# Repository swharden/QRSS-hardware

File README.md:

# QRSS Hardware

This repository is an evolving collection of notes and resources related to QRSS hardware (TX and RX) that I (Scott Harden, AJ4VD) find useful. Eventually this work will become a webpage, but for now it's a GitHub repository which makes it easy to edit.

* **[Recently spotted AJ4VD QRSS signals](/spots)**
* Hardware notes are in the [builds](/builds) folder 
* New to QRSS?
  * [What is QRSS?](https://www.qsl.net/m0ayf/What-is-QRSS.html)
  * Join the [_QRSS Knights_ mailing list](https://groups.io/g/qrssknights)
  * See live signals around the world with [QRSS Plus](http://www.swharden.com/qrss/plus/)

### Modular QRSS Transmitter for Experimentation

The transmitter I built uses separate modules. I designed my transmitter this way so I can get a signal on the air, then work toward improving individual modules individually. My current design supports FSK (frequency-shift keying), OOK (on-off keying), and adjustable power output, and synchronization with GPS time. 

Modules are all individually powered and use SMA connectors for inputs/outputs. By applying this [SOLID](https://www.youtube.com/watch?v=TMuno5RZNeE&t=15m50s) principle to hardware development, the system easy to refactor (because it reduces _coupling_) and individual units are easy to test (because they have a defined _interface_).

* **oscillator** - Colpitts, 10.140 MHz crystal, no inductors (so SMT PCB is easy), outputs about 1 mW
* **oscillator oven** - uses two power 50 Ohm resistors to heat the _entire oscillator enclosure_ to above ambient room temperature. Thermistor is used for temperature sensation. By heating an entire metal-enclosed oscillator module, the entire oscillator circuitry (not just the crystal) becomes thermo-stable.
* **keyer** - based on an ATTiny2313 microcontroller. Keying is pulse-width modulated (PWM), and OOK output is also provided. Keyer has voltage combiner which has separate knobs to adjust center frequency and FSK width. Output is a single voltage for the oscillator, and a signal voltage for the amplifier. While it's currently configured for OOK, an analog voltage could be sent to the amplifier to control power output from software.
* **GPS** - To start messages at precise 10 minute intervals a GPS module (Neo-6M) is used. Rather than tap into the 1PPS signal line, I'm using the microcontroller to parse the serial data coming off the chip and begin transmitting at precise times.
* **amplifier** - currently an IRF510 final transistor with  74HC541 buffer pre-amplifier. The 74HC541's enable lines are controlled by the keyer to provide OOK. A potentiometer sets the power output. The current design has been tested to over 10W but this is an unnecessary (and undesirable) power level for QRSS.
* **frequency counter** - this is an independent project at the moment. I'm creating a USB frequency counter which will be useful for graphing frequency stability over time (and its relationship with temperature). I'll link to this once I have it tested/working.
* **antenna** - 30m dipole in my attic (Gainesville, Florida, USA)

### Photographs

This is a work in progress so the enclosures (if they even exist) are pretty crude. Additional photographs (and schematics) at various stages of the design process can be found in sub-folders of this repository. As individual modules are improved, these photographs will be updated.

### Project goals

I experimented with QRSS on and off over the last decade, but all of my designs were pretty crude. Now that I have more experience, knowledge, and resources, I'd like to get back into the hobby.

There are a lot of crystal oven designs and chassis heater designs out there, and I'd like to get better at testing different designs. This requires precision temperature and frequency measurements and involves using a PC for data-logging and analysis. I'd like to get a better understanding of the temperature vs. frequency profile not just of crystals, but of the entire oscillator circuit. I'm interested in developing a SMT oscillator board with the temperature controller built-in (using SMT resistors to heat the PCB, temperature-stabilizing the entire oscillator rather than just the crystal).

I'd also like to improve QRSS Plus, and see about creating an open-source QRSS spectrograph like Argo now that I have experience developing Windows applications with C#. While my previous efforts (in Python) were interesting, I now have a strong appreciation for click-to-run software that works with minimal complexity.

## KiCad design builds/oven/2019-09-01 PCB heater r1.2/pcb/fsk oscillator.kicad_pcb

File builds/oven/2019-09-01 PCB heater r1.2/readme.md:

# PCB Heater r1.2

The ultimate goal is to create a thermo-stable oscillator by heating the PCB to above ambient temperature (about 120F). This board tests how effective 8x 330 Ohm resistors can be at heating a 5cm x 5cm PCB. 

* A 10K NTC thermistor senses temperature in the center of the board
* At 12V each 330 Ohm resistor passes 36.3 mA (437 mW)
* Total max heating power is around 3.5 W
* The transistor also serves as a heating element

## Build Notes

_I ordered this board on 2019-09-01_

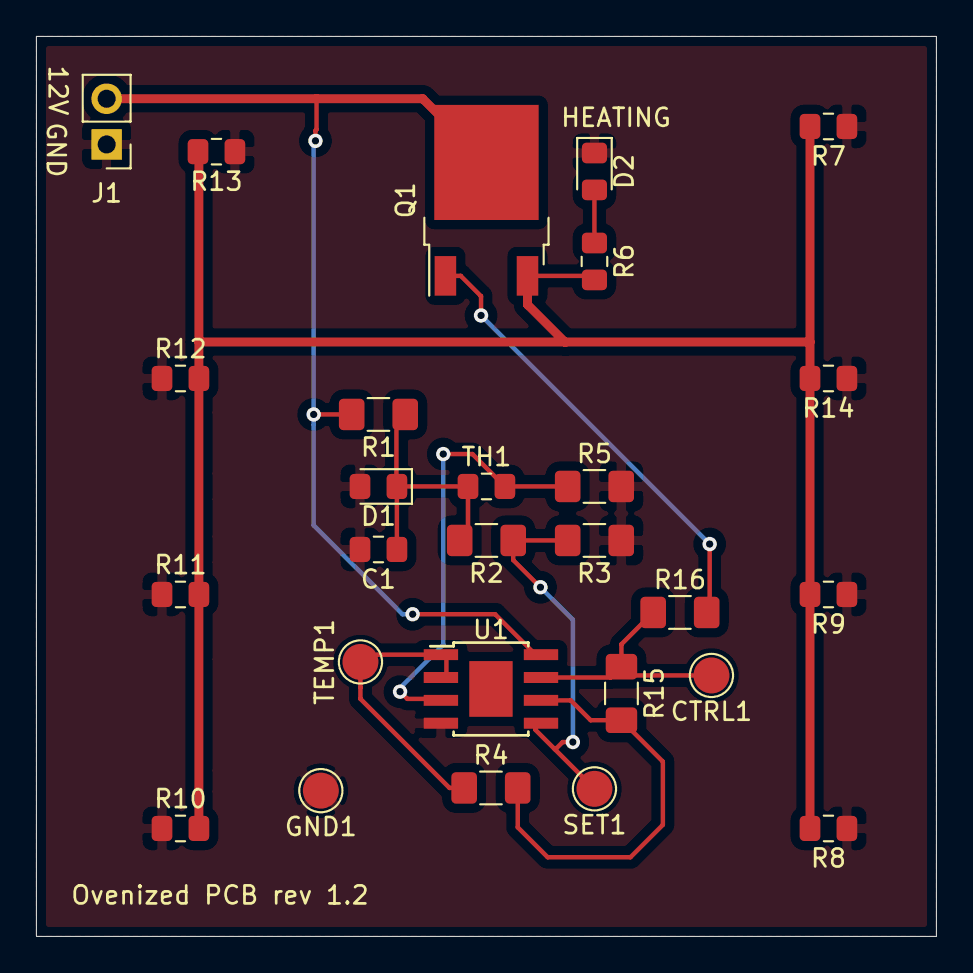
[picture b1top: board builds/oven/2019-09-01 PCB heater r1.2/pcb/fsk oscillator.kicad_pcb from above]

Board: 2 copper layers, 50.0 x 50.0 mm, 27 parts (0 on the bottom side), 11 nets.

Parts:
C1: .1u; C_0805_2012Metric_Pad1.15x1.40mm_HandSolder
CTRL1: TestPoint; TestPoint_Pad_D2.0mm
D1: 10V; D_0805_2012Metric_Pad1.15x1.40mm_HandSolder
D2: HEATING; LED_0805_2012Metric_Pad1.15x1.40mm_HandSolder
GND1: TestPoint; TestPoint_Pad_D2.0mm
J1: Conn_01x02_Male; PinHeader_1x02_P2.54mm_Vertical
Q1: MJD122; TO-252-2
R1, R4, R16: 1k; R_1206_3216Metric_Pad1.42x1.75mm_HandSolder
R2, R3, R5, R15: 10k; R_1206_3216Metric_Pad1.42x1.75mm_HandSolder
R6: 10k; R_0805_2012Metric_Pad1.15x1.40mm_HandSolder
R7, R8, R9, R10, R11, R12, R13, R14: 330; R_0805_2012Metric_Pad1.15x1.40mm_HandSolder
SET1: TestPoint; TestPoint_Pad_D2.0mm
TEMP1: TestPoint; TestPoint_Pad_D2.0mm
TH1: NTC; R_0805_2012Metric_Pad1.15x1.40mm_HandSolder
U1: LM358_DFN; TI_SO-PowerPAD-8

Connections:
+12V: J1.2, Q1.2, R1.2, U1.8
GND: C1.2, D1.2, D2.1, GND1.1, J1.1, R3.1, R5.2, R7.1, R8.1, R9.1, R10.1, R11.1, R12.1, R13.1, R14.1, U1.4
unnamed: CTRL1.1, R15.1, R16.1, U1.7
unnamed: D2.2, R6.1
unnamed: Q1.1, R16.2
unnamed: Q1.3, R6.2, R7.2, R8.2, R9.2, R10.2, R11.2, R12.2, R13.2, R14.2
unnamed: R2.1, R3.2, SET1.1, U1.5
unnamed: R4.1, TEMP1.1, U1.1, U1.2
unnamed: R5.1, TH1.2, U1.3
unnamed: R4.2, R15.2, U1.6
REF: C1.1, D1.1, R1.1, R2.2, TH1.1

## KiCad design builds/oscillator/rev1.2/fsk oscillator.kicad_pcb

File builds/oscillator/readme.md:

# QRSS Oscillator

This page documents development of a voltage-controlled oscillator suitable for QRSS. The oscillator project is developed in concert with the oven project.

## Varactor FSK Designs for QRSS

For QRSS it's convenient to have 2 frequency shift adjustments: a coarse one to set frequency (~200 Hz), and a fine one for FSK (5 Hz). 

Most QRSS TX designs use a variable capacitor to set the coarse adjustment, but I don't like that design because it means you have to open your enclosure every time you want to shift frequency:

VK2ZAY shows a design that pulls one leg of a crystal using two varactors, the magnitude of each is controlled by a series capacitor:

I tried building designs like this I find them very frustrating. 

Issue 1: coarse adjustment modifies FSK shift.
Every time I adjust the coarse voltage, the FSK distance changes. Consider a coarse adjustment resulting in a small capacitance: the fine FSK can produce a large shift. When the coarse produces a large capacitance, the fine FSK has little effect. If your fine FSK is a perfect 5Hz and you adjust the coarse frequency, your FSK is no longer 5Hz.

Issue 2: ~varactor diodes are too variable at low voltages. For stable operation it helps to run a varactor at several volts. I fix this by running the FSK voltage through a voltage divider _to VCC_ (not ground), and use the high-pulled fractional voltage on the varactor.~ Actually this was only a problem for reverse-biased LEDs. Real varactor diodes worked fine at low voltages.

***NOTE TO SELF: Use a real varicap diode! You have [BB132](https://uk.rs-online.com/webdocs/0466/0900766b80466490.pdf) (around 60 pF) and [BB149A](http://pdf.datasheetcatalog.com/datasheet/NXP_Semiconductors/BB149A.pdf) (around 20 pF) so you can get tons of swing by using one! Stop using reverse-biased LEDs!*** A reverse-biasd blue LED measured 60 Hz swing (with a lot of additional fixed capacitance in place to get near center frequency). Replacing this with a BB132 (I had to remove a 5pA cap to compensate) I got a swing of 159 Hz. That's more than double, and that's just one varicap. You can stack them in parallel. **Real varicaps dont mind low voltage*** I found out, so don't worry about avoiding that super low region like with the LED.

This is a design I came up with that seems to be treating me well so far. Fixed capacitors (optionally populated) set the frequency so the crystal oscillates in the QRSS band. The coarse adjustment moves the signal around the QRSS band (100Hz). The fine adjustment is pulled high through a divider. Adjust R4 to control how wide the FSK can be.

## QRSS Oscillator Revision 1.1

### Design

### Build Notes

* I used BB132 for the varicap
* I used 33P for C6
* For C9 I used 33p (should be NP0)
* For C11 I used 100p
* For C10 and C12 I used NP0 120p caps

## QRSS Oscillator Revision 1.2

This version has the oven built into the PCB.
The oven controller is still external.
Not sure how many resistors need to actually be populated for the oven.
I ordered this PCB on 2019-07-28.

### Design

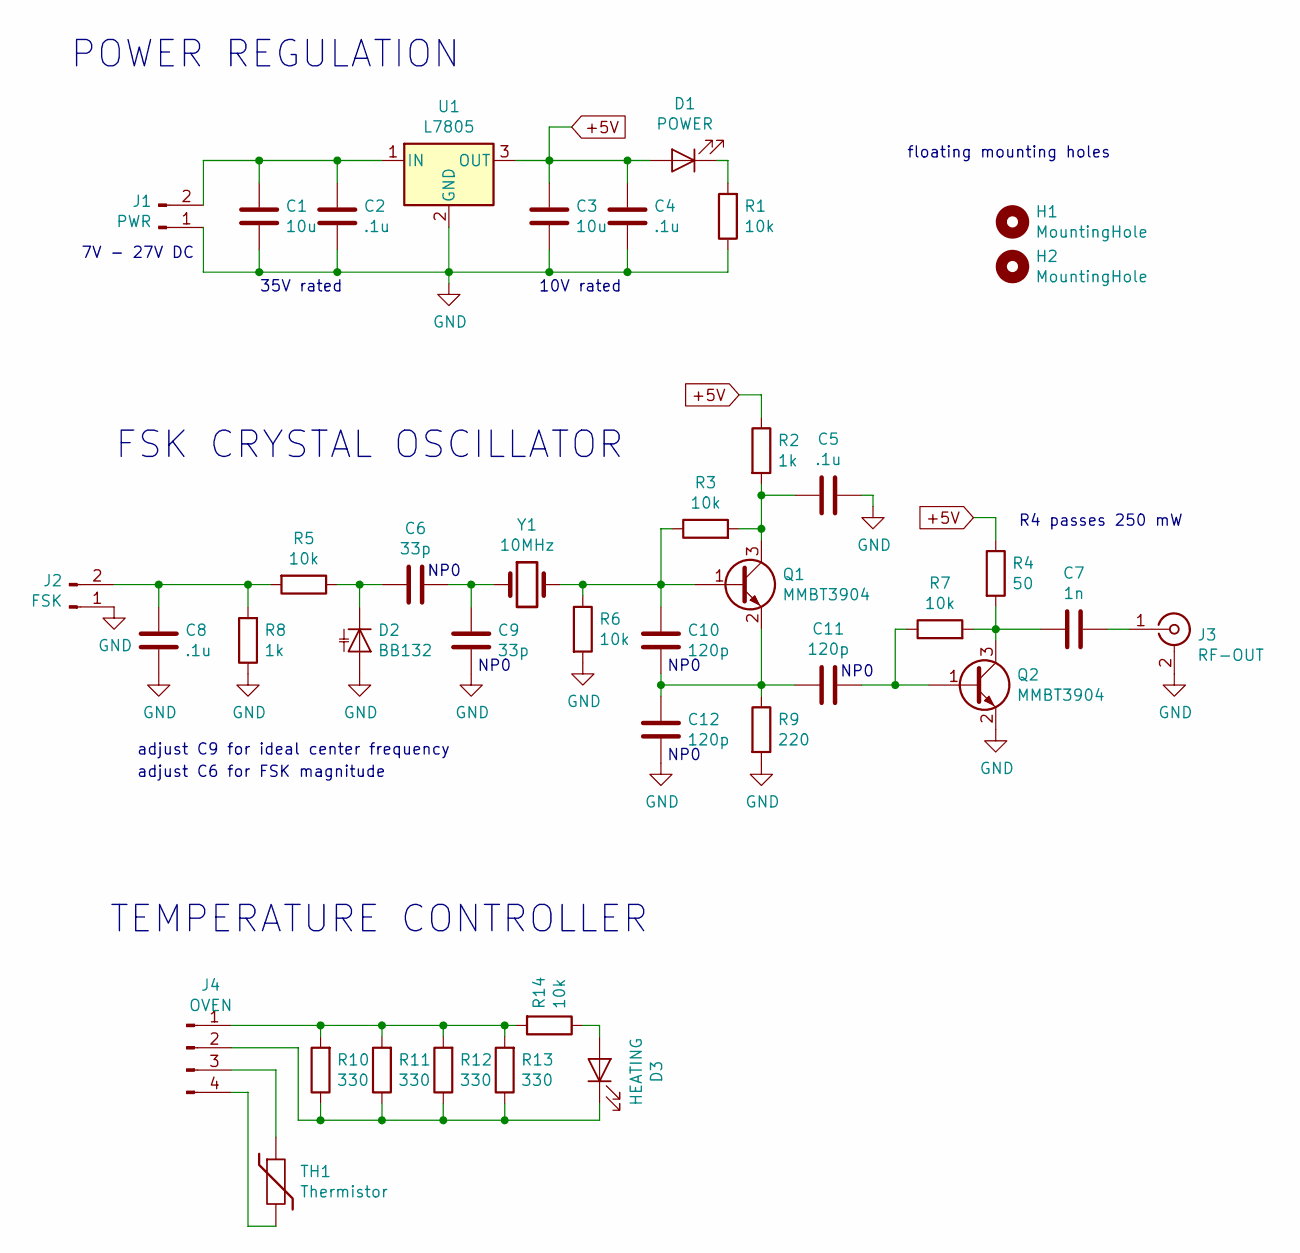
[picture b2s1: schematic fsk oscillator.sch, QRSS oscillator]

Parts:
C1, C3: 10u; C_0805_2012Metric_Pad1.15x1.40mm_HandSolder
C2, C4, C5, C8: .1u; C_0805_2012Metric_Pad1.15x1.40mm_HandSolder
C6, C9: 33p; C_0805_2012Metric_Pad1.15x1.40mm_HandSolder
C7: 1n; C_0805_2012Metric_Pad1.15x1.40mm_HandSolder
C10, C11, C12: 120p; C_0805_2012Metric_Pad1.15x1.40mm_HandSolder
D1: POWER; LED_0805_2012Metric_Pad1.15x1.40mm_HandSolder
D2: BB132; LED_0805_2012Metric_Pad1.15x1.40mm_HandSolder
D3: HEATING; LED_0805_2012Metric_Pad1.15x1.40mm_HandSolder
H1, H2: MountingHole; MountingHole_4.3mm_M4_Pad_Via
J1: PWR; PinHeader_1x02_P2.54mm_Vertical
J2: FSK; PinHeader_1x02_P2.54mm_Vertical
J3: RF-OUT; SMA_Amphenol_132134-16_Vertical
J4: OVEN; PinHeader_1x04_P2.54mm_Vertical
Q1, Q2: MMBT3904; SOT-23
R1, R3, R5, R6, R7, R14: 10k; R_0805_2012Metric_Pad1.15x1.40mm_HandSolder
R2, R8: 1k; R_0805_2012Metric_Pad1.15x1.40mm_HandSolder
R4: 50; R_1206_3216Metric_Pad1.42x1.75mm_HandSolder
R9: 220; R_0805_2012Metric_Pad1.15x1.40mm_HandSolder
R10, R11, R12, R13: 330; R_0805_2012Metric_Pad1.15x1.40mm_HandSolder
TH1: Thermistor; R_0805_2012Metric_Pad1.15x1.40mm_HandSolder
U1: L7805; TO-252-3_TabPin2
Y1: 10MHz; Crystal_HC49-U_Horizontal_1EP_style2

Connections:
+5V: C3.1, C4.1, D1.2 (A), R2.1, R4.1, U1.3 (OUT)
GND: C1.2, C2.2, C3.2, C4.2, C5.1, C8.2, C9.2, C12.2, D2.2 (A), J1.1, J2.1, J3.2 (Ext), Q2.2 (E), R1.1, R6.2, R8.1, R9.2, U1.2 (GND); also elsewhere on the board
unnamed 2: C1.1, C2.1, J1.2, U1.1 (IN); also elsewhere on the board
unnamed: C5.2, Q1.3 (C), R2.2, R3.2
unnamed: C6.1, D2.1 (K), R5.1
unnamed: C6.2, C9.1, Y1.1
unnamed: C7.1, J3.1 (In)
unnamed: C7.2, Q2.3 (C), R4.2, R7.2
unnamed 8: C8.1, J2.2, R5.2, R8.2; also elsewhere on the board
unnamed: C10.1, Q1.1 (B), R3.1, R6.1, Y1.2
unnamed: C10.2, C11.2, C12.1, Q1.2 (E), R9.1
unnamed: C11.1, Q2.1 (B), R7.1
unnamed: D1.1 (K), R1.2
unnamed 13: D3.1 (K), J4.2, R10.1, R11.1, R12.1, R13.1; also elsewhere on the board
unnamed 14: D3.2 (A), R14.1; also elsewhere on the board
unnamed 15: J4.1, R10.2, R11.2, R12.2, R13.2, R14.2; also elsewhere on the board
unnamed 16: J4.3, TH1.1; also elsewhere on the board
unnamed 17: J4.4, TH1.2; also elsewhere on the board

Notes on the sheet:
POWER REGULATION
7V - 27V DC
adjust C6 for FSK magnitude
adjust C9 for ideal center frequency
FSK CRYSTAL OSCILLATOR
R4 passes 250 mW
floating mounting holes
35V rated
10V rated
NP0
TEMPERATURE CONTROLLER

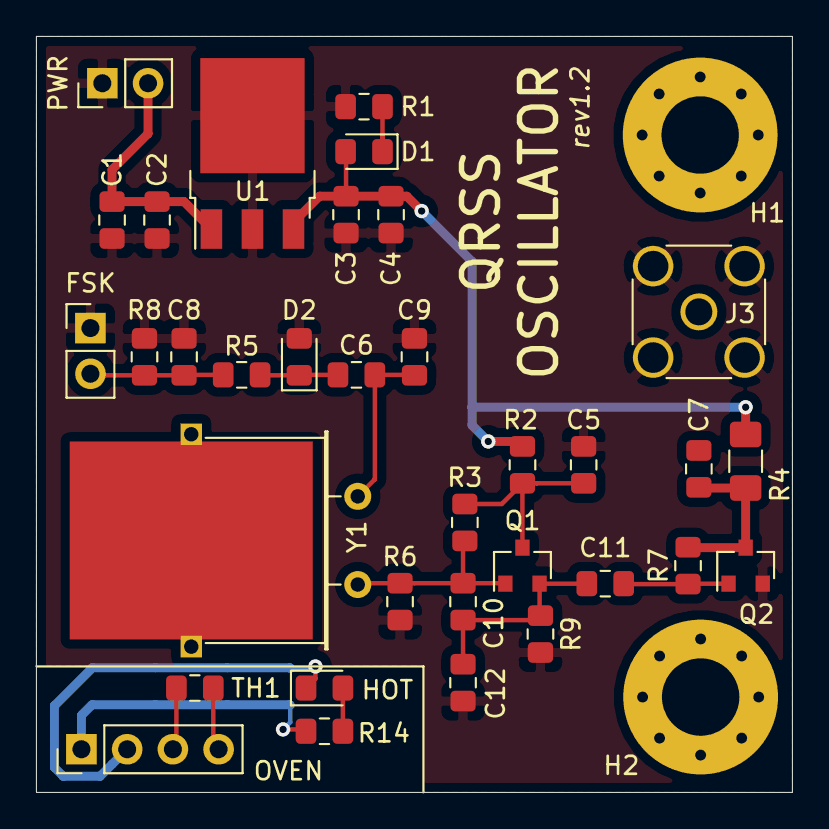
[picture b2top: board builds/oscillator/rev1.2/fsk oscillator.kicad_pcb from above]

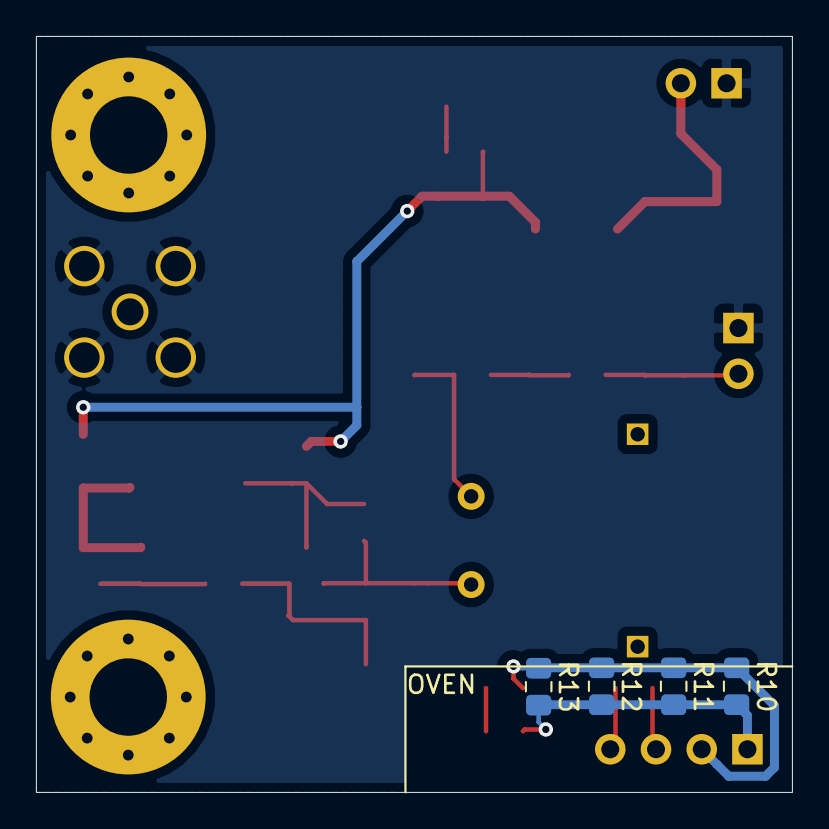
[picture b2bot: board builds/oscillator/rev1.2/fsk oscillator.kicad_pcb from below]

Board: 2 copper layers, 42.0 x 42.0 mm, 40 parts (4 on the bottom side), 18 nets.

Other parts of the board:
FSK: FSK; PinHeader_1x02_P2.54mm_Vertical
HOT: HEATING; LED_0805_2012Metric_Pad1.15x1.40mm_HandSolder
OVEN: OVEN; PinHeader_1x04_P2.54mm_Vertical
PWR: PWR; PinHeader_1x02_P2.54mm_Vertical

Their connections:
GND: FSK.1, PWR.1; also elsewhere on the board
unnamed 2: PWR.2; also elsewhere on the board
unnamed 8: FSK.2; also elsewhere on the board
unnamed 13: HOT.1, OVEN.2; also elsewhere on the board
unnamed 14: HOT.2; also elsewhere on the board
unnamed 15: OVEN.1; also elsewhere on the board
unnamed 16: OVEN.3; also elsewhere on the board
unnamed 17: OVEN.4; also elsewhere on the board

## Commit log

2019-07-12 initial upload
2019-07-13 refactor
2019-07-14 varactor notes
2019-07-14 lazy oven
2019-07-15 crystal oven
2019-07-15 chassis heater notes
2019-07-15 improve grabs
2019-07-15 fix schematic
2019-07-15 update spots readme
2019-07-15 update spot
2019-07-17 update keyer pattern
2019-07-19 S pattern TX
2019-07-19 new spots
2019-07-19 improve splash page
2019-07-20 74HC541 notes
2019-07-20 additional photographs
2019-07-20 module diagram
2019-07-20 update keyer code to wait for GPS times
2019-07-20 update keyer code to start on 0 and 5 min
2019-07-20 transmit slower and only once per ten minutes
2019-07-20 transmit slower
2019-07-20 update spots
2019-07-21 fixed spot folder names
2019-07-21 store screenshot locally
2019-07-21 update keyer notes
2019-07-27 more grabs
2019-07-27 add build photos
2019-07-28 crazy math
2019-07-28 ovenize pcb
2019-07-28 update resistor info
2019-07-31 added spot in Africa
2019-08-01 updated amplifier design
2019-08-01 add amplifier schematic
2019-08-01 update canada spot
2019-08-01 add keyer photos
2019-08-03 new spot
2019-08-29 start pcb heater
2019-09-01 pcb oven r1.2
2019-09-03 updated grab
